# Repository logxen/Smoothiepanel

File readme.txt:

SmoothiePanel is an Open Source Hardware control interface for industrial robotic machinery. It adds a screen and user interface to allow easy control of a Smoothieboard. The current design brings a graphic LCD with RGB Backlight and changeable interface panel down to a port, optionally SPI, UART, or USB.

It is intended to control a Smoothieboard (http://smoothieware.org/), though could easily be connected to almost any logic control system. The firmware found in the firmware directory makes Smoothiepanel behave as a simple slave device that can be used via SPI, UART, or USB. As it is completely open source, however, it is very easy to write custom firmware that takes more advantage of its powerful 50MHz processor and 16 bits worth of extra gpio.

The latest version, Prototype 3, is based around the NXP LPC11UxxFBD64, which sports a 50MHz ARM Cortex-M0 processor with built in USB and up to 128KB of flash.

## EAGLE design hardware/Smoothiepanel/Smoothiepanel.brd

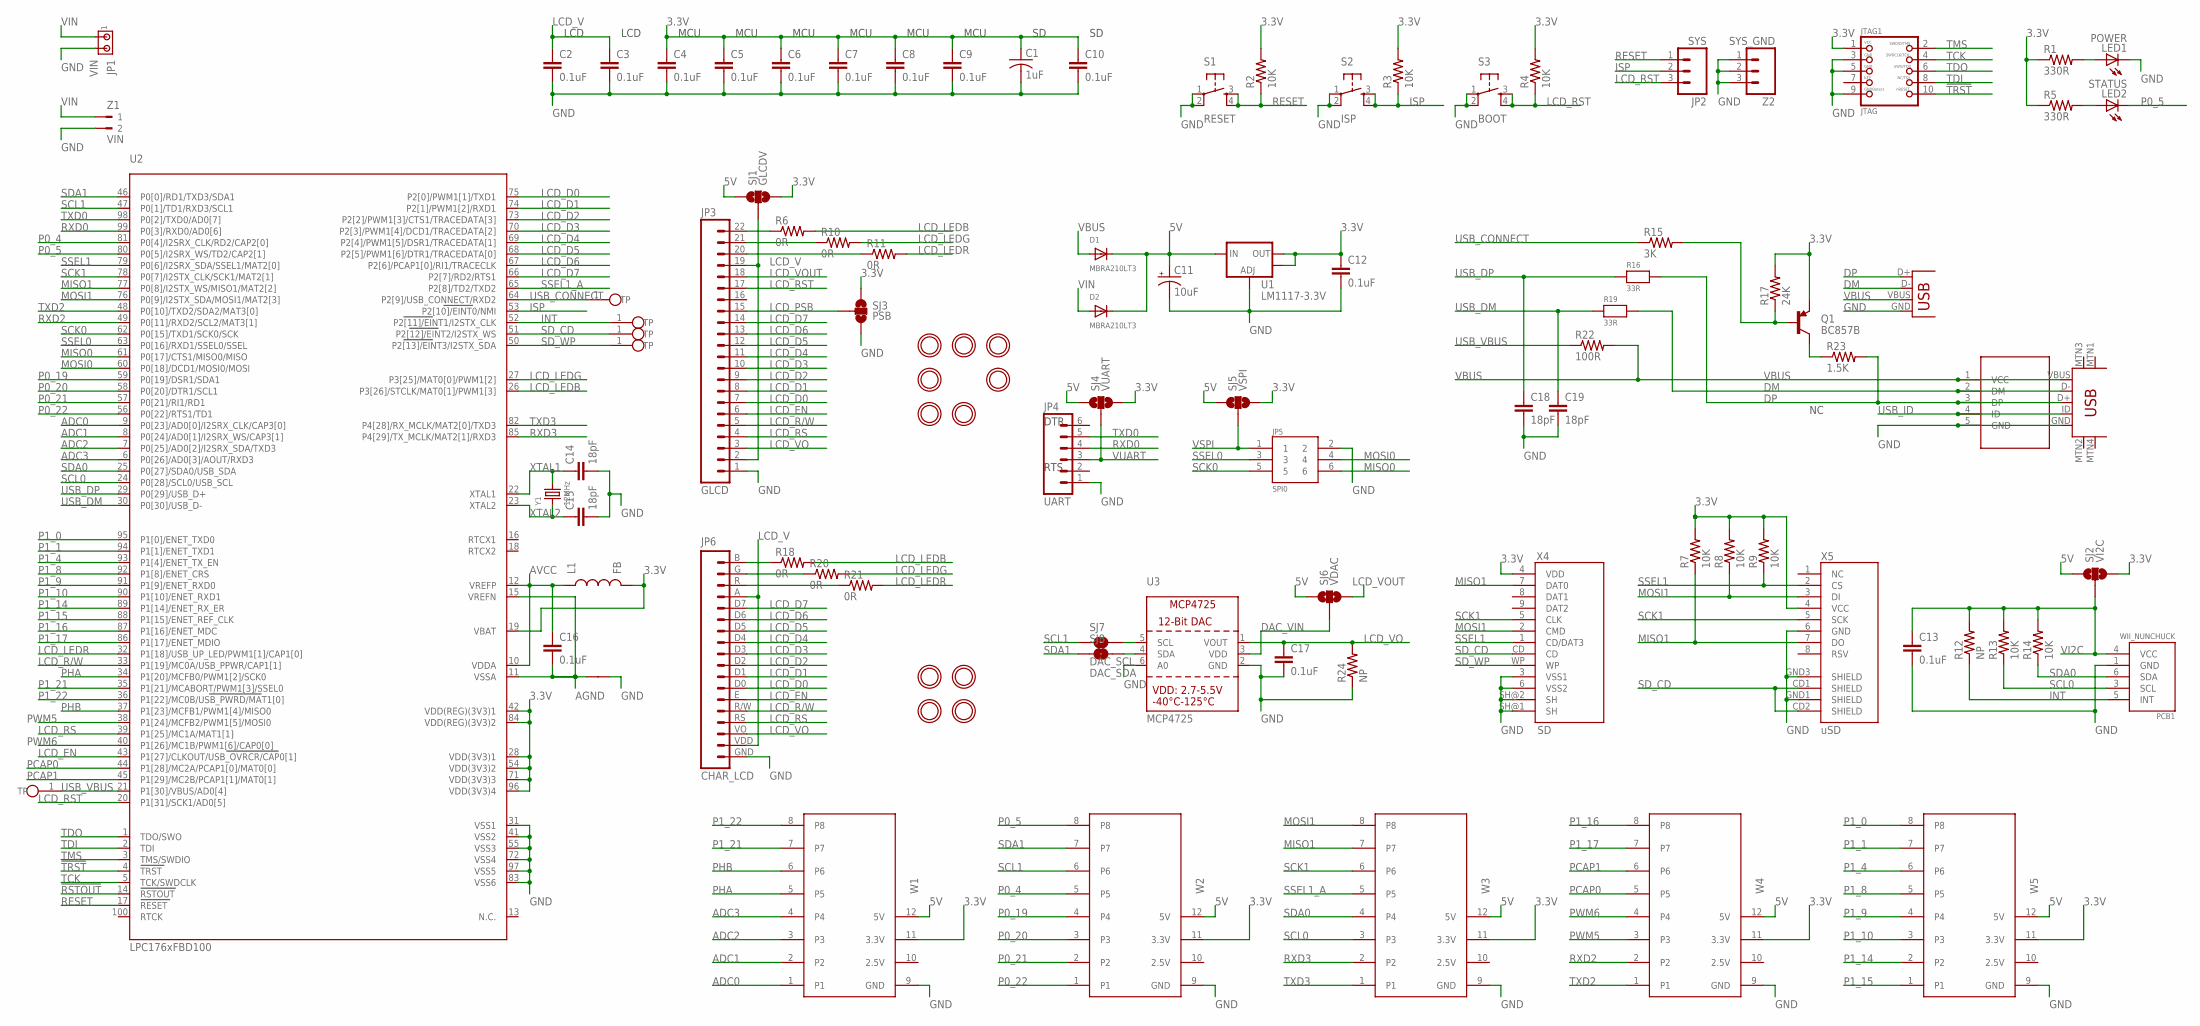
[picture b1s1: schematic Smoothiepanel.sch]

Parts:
C1: 1uF; C0805
C2, C3, C4, C5, C6, C7, C8, C9, C10, C12, C13, C16, C17: 0.1uF; 0603-CAP
C11: 10uF; EIA3216
C14, C15, C18, C19: 18pF; 0603-CAP
D1, D2: MBRA210LT3; SMADIODE
JP1: VIN; 10X02MTA
JP2: SYS; 1X03
JP3: GLCD; 1X22
JP4: UART; 1X06
JP5: SPI0; 2X3-SHROUDED
JP6: CHAR_LCD; TEXT_LCD
JTAG1: JTAG; 2X05_1.27MM_SMT
L1: FB; 0603
LED1: POWER; LED-0603
LED2: STATUS; LED-0603
MH1, MH2, MH3, MH4, MH5, MH6, MH7: MOUNTINGHOLE2.5_THICK; MOUNTINGHOLE_2.5_PLATED_THICK
MH8, MH9, MH10, MH11: MOUNTINGHOLE3.0THIN; MOUNTINGHOLE_3.0_PLATEDTHIN
N1: NET_LINK
PCB1: WII_NUNCHUCK
Q1: BC857B; SOT23-3
R1, R5: 330R; 0603-RES
R2, R3, R4, R7, R8, R9, R13, R14: 10K; 0603-RES
R6, R10, R11, R18, R20, R21: 0R; 0603-RES
R12, R24: NP; 0603-RES
R15: 3K; 0603-RES
R16, R19: 33R; _0603MP
R17: 24K; 0603-RES
R22: 100R; 0603-RES
R23: 1.5K; 0603-RES
S1: RESET; TACTILE_SWITCH_SMD
S2: ISP; TACTILE_SWITCH_SMD
S3: BOOT; TACTILE_SWITCH_SMD
SJ1: GLCDV; SJ_3
SJ2: VI2C; SJ_3
SJ3: PSB; SJ_3
SJ4: VUART; SJ_3
SJ5: VSPI; SJ_3
SJ6: VDAC; SJ_3
SJ7: DAC_SCL; SJ_2S-TRACE
SJ8: DAC_SDA; SJ_2S-TRACE
TP1, TP3, TP4, TP5, TP6: TPAD1.5; TPAD-1.5
U1: LM1117-3.3V; SOT223
U2: LPC176xFBD100; LQFP100
U3: MCP4725; SOT23-6
W1: WING1; PAPILIO-WING-8BITS-F
W2: WING2; PAPILIO-WING-8BITS-F
W3: WING3; PAPILIO-WING-8BITS-F
W4: WING4; PAPILIO-WING-8BITS-F
W5: WING5; PAPILIO-WING-8BITS-F
X1: USB-B; USB-B-PTH
X2: mUSB; USB-MINIB
X3: USB-MICROB-SMDRECEPT; USB-MICROB-RECEPT
X4: SD; SDCARD_4UCONN
X5: uSD; MICRO-SD-SOCKET-PP
Y1: 12MHz; CRYSTAL_3.2X2.5
Z1: VIN; 180-2
Z2: SYS_GND; 1X03

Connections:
3.3V: C1.1, C4.1, C5.1, C6.1, C7.1, C8.1, C9.1, C10.1, C12.1, JTAG1.1, L1.2, Q1.2 (E), R1.1, R2.2, R3.2, R4.2, R5.1, R7.2, R8.2, R9.2, R17.2, SJ1.3, SJ2.3, SJ3.1, SJ4.3, SJ5.3, U1.2 (OUT), U1.4 (OUT), U2.19 (VBAT), U2.28 (VDD(3V3)1), U2.42 (VDD(REG)(3V3)1), U2.54 (VDD(3V3)2), U2.71 (VDD(3V3)3), U2.84 (VDD(REG)(3V3)2), U2.96 (VDD(3V3)4), W1.11 (3.3V), W2.11 (3.3V), W3.11 (3.3V), W4.11 (3.3V), W5.11 (3.3V), X4.4 (VDD), X5.4 (VCC)
5V: C11.A (+), D1.C, D2.C, SJ1.1, SJ2.1, SJ4.1, SJ5.1, SJ6.1, U1.3 (IN), W1.12 (5V), W2.12 (5V), W3.12 (5V), W4.12 (5V), W5.12 (5V)
!RSTOUT!: U2.14 (RSTOUT)
!TRST!: JTAG1.10, U2.4 (TRST)
ADC0: U2.9 (P0[23]/AD0[0]/I2SRX_CLK/CAP3[0]), W1.1
ADC1: U2.8 (P0[24]/AD0[1]/I2SRX_WS/CAP3[1]), W1.2
ADC2: U2.7 (P0[25]/AD0[2]/I2SRX_SDA/TXD3), W1.3
ADC3: U2.6 (P0[26]/AD0[3]/AOUT/RXD3), W1.4
AGND: C16.2, N1.P$1, U2.11 (VSSA), U2.15 (VREFN)
AVCC: C16.1, L1.1, U2.10 (VDDA), U2.12 (VREFP)
DAC_SCL_RES: SJ7.2, U3.5 (SCL)
DAC_SDA_RES: SJ8.2, U3.4 (SDA)
DAC_VIN: SJ6.2, U3.3 (VDD)
DM: R19.2, X1.D-, X2.D-, X3.2 (DM)
DP: R16.2, R23.2, X1.D+, X2.D+, X3.3 (DP)
GND: C1.2, C2.2, C3.2, C4.2, C5.2, C6.2, C7.2, C8.2, C9.2, C10.2, C11.C (-), C12.2, C13.2, C14.2, C15.2, C17.2, C18.2, C19.2, JP1.2, JP3.1, JP4.1, JP5.2, JP6.GND (1), JTAG1.3, JTAG1.5, JTAG1.9, LED1.C, N1.P$2, PCB1.1 (GND), R24.1, S1.1, S1.2, S2.1, S2.2, S3.1, S3.2, SJ3.3, U1.1 (ADJ), U2.31 (VSS1), U2.41 (VSS2), U2.55 (VSS3), U2.72 (VSS4), U2.83 (VSS6), U2.97 (VSS5), U3.2 (GND), U3.6 (A0), W1.9 (GND), W2.9 (GND), W3.9 (GND), W4.9 (GND), W5.9 (GND), X1.GND, X2.GND, X3.5 (GND), X4.3 (VSS1), X4.6 (VSS2), X4.SH@1 (SH), X4.SH@2 (SH), X5.6 (GND), X5.GND1 (SHIELD), X5.GND3 (SHIELD), Z1.2, Z2.1, Z2.2, Z2.3
INT: PCB1.5 (INT), R12.1, TP4.1, U2.52 (P2[11]/EINT1/I2STX_CLK)
ISP: JP2.2, R3.1, S2.3, S2.4, U2.53 (P2[10]/EINT0/NMI)
LCD_D0: JP3.7, JP6.D0 (7), U2.75 (P2[0]/PWM1[1]/TXD1)
LCD_D1: JP3.8, JP6.D1 (8), U2.74 (P2[1]/PWM1[2]/RXD1)
LCD_D2: JP3.9, JP6.D2 (9), U2.73 (P2[2]/PWM1[3]/CTS1/TRACEDATA[3])
LCD_D3: JP3.10, JP6.D3 (10), U2.70 (P2[3]/PWM1[4]/DCD1/TRACEDATA[2])
LCD_D4: JP3.11, JP6.D4 (11), U2.69 (P2[4]/PWM1[5]/DSR1/TRACEDATA[1])
LCD_D5: JP3.12, JP6.D5 (12), U2.68 (P2[5]/PWM1[6]/DTR1/TRACEDATA[0])
LCD_D6: JP3.13, JP6.D6 (13), U2.67 (P2[6]/PCAP1[0]/RI1/TRACECLK)
LCD_D7: JP3.14, JP6.D7 (14), U2.66 (P2[7]/RD2/RTS1)
LCD_EN: JP3.6, JP6.E (6), U2.43 (P1[27]/CLKOUT/USB_OVRCR/CAP0[1])
LCD_LEDB: R6.2, R18.2, U2.26 (P3[26]/STCLK/MAT0[1]/PWM1[3])
LCD_LEDB_RES: JP3.22, R6.1
LCD_LEDB_RES1: JP6.B (18), R18.1
LCD_LEDG: R10.2, R20.2, U2.27 (P3[25]/MAT0[0]/PWM1[2])
LCD_LEDG_RES: JP3.21, R10.1
LCD_LEDG_RES1: JP6.G (17), R20.1
LCD_LEDR: R11.2, R21.2, U2.32 (P1[18]/USB_UP_LED/PWM1[1]/CAP1[0])
LCD_LEDR_RES: JP3.20, R11.1
LCD_LEDR_RES1: JP6.R (16), R21.1
LCD_PSB: JP3.15, SJ3.2
LCD_R/W: JP3.5, JP6.R/W (5), U2.33 (P1[19]/MC0A/USB_PPWR/CAP1[1])
LCD_RS: JP3.4, JP6.RS (4), U2.39 (P1[25]/MC1A/MAT1[1])
LCD_RST: JP2.3, JP3.17, R4.1, S3.3, S3.4, U2.20 (P1[31]/SCK1/AD0[5])
LCD_V: C2.1, C3.1, JP3.2, JP3.19, JP6.A (15), JP6.VDD (2), SJ1.2
LCD_VO: C17.1, JP3.3, JP6.VO (3), R24.2, U3.1 (VOUT)
LCD_VOUT: JP3.18, SJ6.3
LED1_R: LED1.A, R1.2
LED2_R: LED2.A, R5.2
MISO0: JP5.6, U2.61 (P0[17]/CTS1/MISO0/MISO)
MISO1: R7.1, U2.77 (P0[8]/I2STX_WS/MISO1/MAT2[2]), W3.7, X4.7 (DAT0), X5.7 (DO)
MOSI0: JP5.4, U2.60 (P0[18]/DCD1/MOSI0/MOSI)
MOSI1: R8.1, U2.76 (P0[9]/I2STX_SDA/MOSI1/MAT2[3]), W3.8, X4.2 (CMD), X5.3 (DI)
P0_4: U2.81 (P0[4]/I2SRX_CLK/RD2/CAP2[0]), W2.5
P0_5: LED2.C, U2.80 (P0[5]/I2SRX_WS/TD2/CAP2[1]), W2.8
P0_19: U2.59 (P0[19]/DSR1/SDA1), W2.4
P0_20: U2.58 (P0[20]/DTR1/SCL1), W2.3
P0_21: U2.57 (P0[21]/RI1/RD1), W2.2
P0_22: U2.56 (P0[22]/RTS1/TD1), W2.1
P1_0: U2.95 (P1[0]/ENET_TXD0), W5.8
P1_1: U2.94 (P1[1]/ENET_TXD1), W5.7
P1_4: U2.93 (P1[4]/ENET_TX_EN), W5.6
P1_8: U2.92 (P1[8]/ENET_CRS), W5.5
P1_9: U2.91 (P1[9]/ENET_RXD0), W5.4
P1_10: U2.90 (P1[10]/ENET_RXD1), W5.3
P1_14: U2.89 (P1[14]/ENET_RX_ER), W5.2
P1_15: U2.88 (P1[15]/ENET_REF_CLK), W5.1
P1_16: U2.87 (P1[16]/ENET_MDC), W4.8
P1_17: U2.86 (P1[17]/ENET_MDIO), W4.7
P1_21: U2.35 (P1[21]/MCABORT/PWM1[3]/SSEL0), W1.7
P1_22: U2.36 (P1[22]/MC0B/USB_PWRD/MAT1[0]), W1.8
PCAP0: U2.44 (P1[28]/MC2A/PCAP1[0]/MAT0[0]), W4.5
PCAP1: U2.45 (P1[29]/MC2B/PCAP1[1]/MAT0[1]), W4.6
PHA: U2.34 (P1[20]/MCFB0/PWM1[2]/SCK0), W1.5
PHB: U2.37 (P1[23]/MCFB1/PWM1[4]/MISO0), W1.6
PWM5: U2.38 (P1[24]/MCFB2/PWM1[5]/MOSI0), W4.3
PWM6: U2.40 (P1[26]/MC1B/PWM1[6]/CAP0[0]), W4.4
RESET: JP2.1, R2.1, S1.3, S1.4, U2.17 (RESET)
RXD0: JP4.4, U2.99 (P0[3]/RXD0/AD0[6])
RXD2: U2.49 (P0[11]/RXD2/SCL2/MAT3[1]), W4.2
RXD3: U2.85 (P4[29]/TX_MCLK/MAT2[1]/RXD3), W3.2
SCK0: JP5.5, U2.62 (P0[15]/TXD1/SCK0/SCK)
SCK1: U2.78 (P0[7]/I2STX_CLK/SCK1/MAT2[1]), W3.6, X4.5 (CLK), X5.5 (SCK)
SCL0: PCB1.3 (SCL), R13.1, U2.24 (P0[28]/SCL0/USB_SCL), W3.3
SCL1: SJ7.1, U2.47 (P0[1]/TD1/RXD3/SCL1), W2.6
SDA0: PCB1.6 (SDA), R14.1, U2.25 (P0[27]/SDA0/USB_SDA), W3.4
SDA1: SJ8.1, U2.46 (P0[0]/RD1/TXD3/SDA1), W2.7
SD_CD: TP5.1, U2.51 (P2[12]/EINT2/I2STX_WS), X4.CD, X5.CD1 (SHIELD), X5.CD2 (SHIELD)
SD_WP: TP6.1, U2.50 (P2[13]/EINT3/I2STX_SDA), X4.WP
SSEL0: JP5.3, U2.63 (P0[16]/RXD1/SSEL0/SSEL)
SSEL1: R9.1, U2.79 (P0[6]/I2SRX_SDA/SSEL1/MAT2[0]), X4.1 (CD/DAT3), X5.2 (CS)
SSEL1_A: U2.65 (P2[8]/TD2/TXD2), W3.5
TCK: JTAG1.4, U2.5 (TCK/SWDCLK)
TDI: JTAG1.8, U2.2 (TDI)
TDO: JTAG1.6, U2.1 (TDO/SWO)
TMS: JTAG1.2, U2.3 (TMS/SWDIO)
TXD0: JP4.5, U2.98 (P0[2]/TXD0/AD0[7])
TXD2: U2.48 (P0[10]/TXD2/SDA2/MAT3[0]), W4.1
TXD3: U2.82 (P4[28]/RX_MCLK/MAT2[0]/TXD3), W3.1
USB_CONNECT: R15.1, TP3.1, U2.64 (P2[9]/USB_CONNECT/RXD2)
USB_CONNECT_BASE: Q1.1 (B), R15.2, R17.1
USB_CONNECT_COLLECTOR: Q1.3 (C), R23.1
USB_DM: C19.1, R19.1, U2.30 (P0[30]/USB_D-)
USB_DP: C18.1, R16.1, U2.29 (P0[29]/USB_D+)
USB_ID: X2.ID, X3.4 (ID)
USB_VBUS: R22.1, TP1.1, U2.21 (P1[30]/VBUS/AD0[4])
VBUS: D1.A, R22.2, X1.VBUS, X2.VBUS, X3.1 (VCC)
VI2C: C13.1, PCB1.4 (VCC), R12.2, R13.2, R14.2, SJ2.2
VIN: D2.A, JP1.1, Z1.1
VSPI: JP5.1, SJ5.2
VUART: JP4.3, SJ4.2
XTAL1: C14.1, U2.22 (XTAL1), Y1.2
XTAL2: C15.1, U2.23 (XTAL2), Y1.1

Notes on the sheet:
DTR
RTS
LCD
MCU

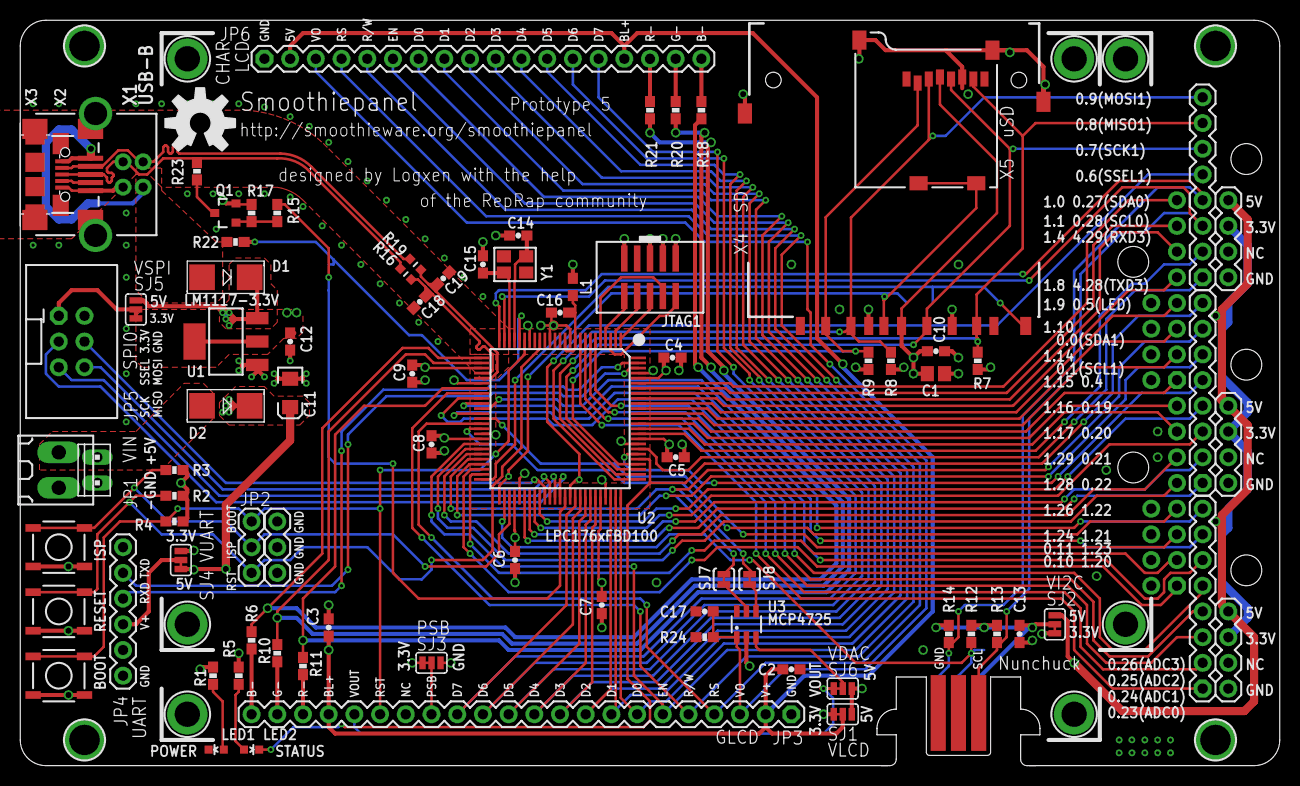
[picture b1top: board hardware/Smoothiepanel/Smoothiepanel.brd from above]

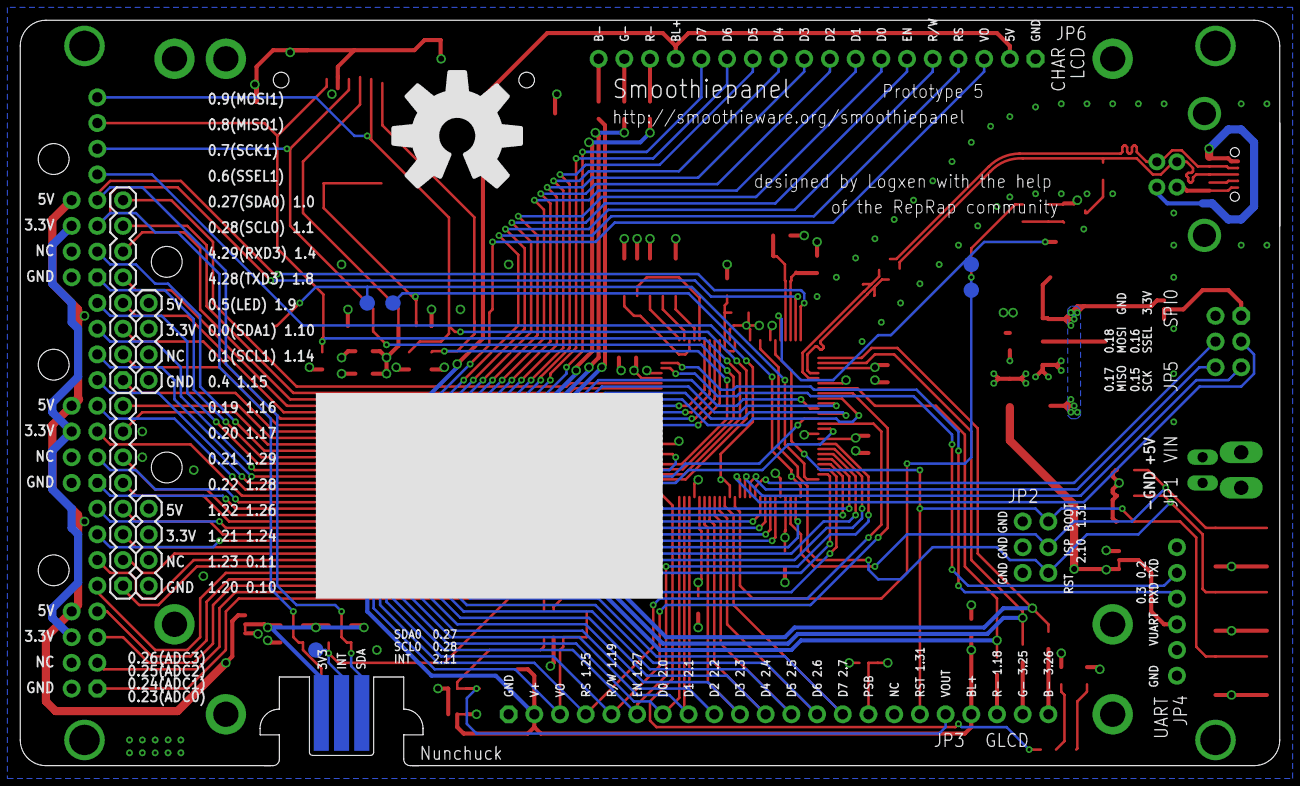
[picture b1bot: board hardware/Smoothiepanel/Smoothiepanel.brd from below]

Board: 4 copper layers, 124.5 x 73.7 mm, 103 parts (8 on the bottom side), 108 nets.

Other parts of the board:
U$1: OSHW-LOGO-HUGE
U$2: OSHW-LOGO-L

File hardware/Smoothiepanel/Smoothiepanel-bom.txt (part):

Partlist exported from C:/Users/Logxen/Documents/eagle/Smoothie/Smoothiepanel/Smoothiepanel/Smoothiepanel-Proto5.sch at 7/15/2014 9:03:24 AM

Qty Value         Device              Package            Parts                                                   Description                                                                                                                                                                                               MF MPN OC_FARNELL OC_NEWARK PROD_ID    VALUE
13  0.1uF         CAP0603-CAP         0603-CAP           C2, C3, C4, C5, C6, C7, C8, C9, C10, C12, C13, C16, C17 Capacitor                                                                                                                                                                                                                                             
6   0R            RESISTOR0603-RES    0603-RES           R6, R10, R11, R18, R20, R21                             Resistor                                                                                                                                                                                                                                              
1   1.5K          RESISTOR0603-RES    0603-RES           R23                                                     Resistor                                                                                                                                                                                                                                              
1   100R          RESISTOR0603-RES    0603-RES           R22                                                     Resistor                                                                                                                                                                                                                                              
8   10K           RESISTOR0603-RES    0603-RES           R2, R3, R4, R7, R8, R9, R13, R14                        Resistor                                                                                                                                                                                                                                              
1   10uF          CAP_POL1206         EIA3216            C11                                                     Capacitor Polarized                                                                                                                                                                                                                                   
1   12MHz         CRYSTALTHIN         CRYSTAL_3.2X2.5    Y1                                                      Crystals                                                                                                                                                                                                                                              
4   18pF          CAP0603-CAP         0603-CAP           C14, C15, C18, C19                                      Capacitor                                                                                                                                                                                                                                             
1   1uF           C-USC0805           C0805              C1                                                      CAPACITOR, American symbol                                                                                                                                                                                                                            
1   24K           RESISTOR0603-RES    0603-RES           R17                                                     Resistor                                                                                                                                                                                                                                              
2   330R          RESISTOR0603-RES    0603-RES           R1, R5                                                  Resistor                                                                                                                                                                                                                                              
2   33R           RESISTOR_0603MP     _0603MP            R16, R19                                                Resistors                                                                                                                                                                                                                                             
1   3K            RESISTOR0603-RES    0603-RES           R15                                                     Resistor                                                                                                                                                                                                                                              
1   BC857B        TRANSISTOR_PNPSMD   SOT23-3            Q1                                                      Generic PNP BJT. Double check pinouts against datasheets- not all devices are the same!                                                                                                                                                               
1   FB            INDUCTOR0603        0603               L1                                                      Inductors                                                                                                                                                                                                                                             
1   LM1117-3.3V   V_REG_LM1117SOT223  SOT223             U1                                                      Voltage Regulator LM1117                                                                                                                                                                                                                              
1   LPC176xFBD100 LPC1768             LQFP100            U2                                                      LPC1768 100 MHz 32-bit ARM Cortex-M3 based microcontroller featuring a high level of integration and low power consumption. 512 kB Flash, 64 kB SRAM, USB Device/Host/OTG, Ethernet, CAN, I2S, 10-bit DAC                                             
2   MBRA210LT3    DIODESMA            SMADIODE           D1, D2                                                  Diode                                                                                                                                                                                                                                                 
1   MCP4725       DAC_MCP4725         SOT23-6            U3                                                      MCP4725 - 12-Bit I2C DAC with on-board EEPROM                                                                                                                                                                                                         
1   POWER         LED0603             LED-0603           LED1                                                    LEDs                                                                                                                                                                                                                                                  
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
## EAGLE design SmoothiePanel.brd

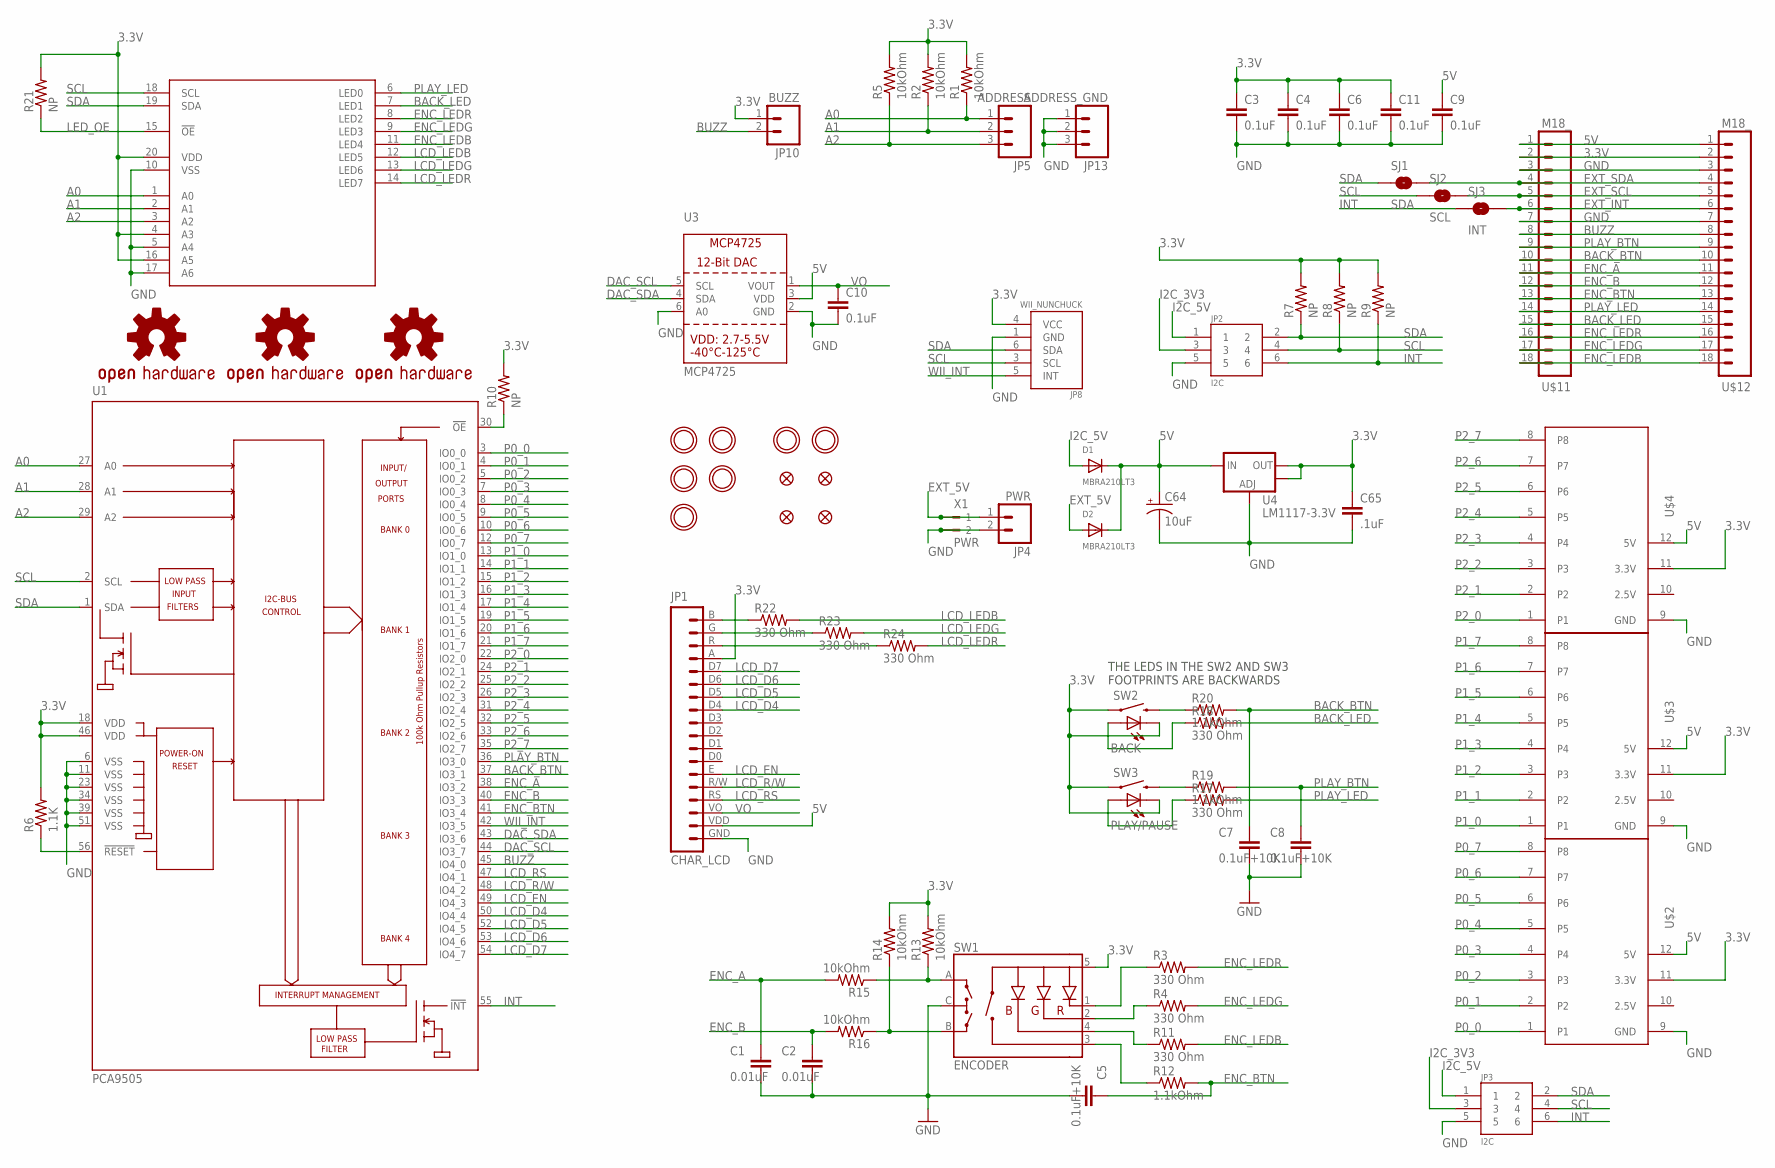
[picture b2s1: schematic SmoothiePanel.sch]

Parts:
C1, C2: 0.01uF; C0603
C3, C4, C6, C9, C10, C11: 0.1uF; 0603-CAP
C5, C7, C8: 0.1uF+10K; C0603
C64: 10uF; EIA3216
C65: .1uF; C0603
D1, D2: MBRA210LT3; SMADIODE
JP1: CHAR_LCD; TEXT_LCD
JP2, JP3: I2C; 2X3-SHROUDED
JP4: PWR; 1X02_LONGPADS
JP5: ADDRESS; 1X03
JP8: WII_NUNCHUCK
JP9, JP11, JP12, JP14: FIDUCIAL1X2; FIDUCIAL-1X2
JP10: BUZZ; 1X02_XTRA_BIG
JP13: ADDRESS_GND; 1X03
R1, R2, R5, R13, R14, R15, R16: 10kOhm; R0603
R3, R4, R11, R17, R18, R22, R23, R24: 330 Ohm; R0603
R6: 1.1K; R0603
R7, R8, R9, R10, R21: NP; R0603
R12, R19, R20: 1.1kOhm; R0603
SJ1: SDA; SJ_2S-NO
SJ2: SCL; SJ_2S-NO
SJ3: INT; SJ_2S-NO
SW1: ENCODER; ENCODER_LED_3
SW2: BACK; TACTILE-PTH-LED-12MM
SW3: PLAY/PAUSE; TACTILE-PTH-LED-12MM
U1: PCA9505; TSSOP56-6
U2: PCA9634-TSSOP20; TSSOP20
U3: MCP4725; SOT23-6
U4: LM1117-3.3V; SOT223
U$1, U$8, U$10: OSHW-LOGOL; OSHW-LOGO-L
U$2, U$3, U$4: PAPILIO-WING-8BITS
U$5, U$9, U$13, U$14, U$15: MOUNTINGHOLE3.0THIN; MOUNTINGHOLE_3.0_PLATEDTHIN
U$6, U$7: MOUNTINGHOLE2.5_THICK; MOUNTINGHOLE_2.5_PLATED_THICK
U$11, U$12: M18_; 1X18
X1: PWR; 180-2

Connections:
3.3V: C3.1, C4.1, C6.1, C11.1, C65.1, JP1.A (15), JP8.4 (VCC), JP10.1, R1.2, R2.2, R5.2, R6.2, R7.2, R8.2, R9.2, R10.2, R13.2, R14.2, R21.2, SW1.5 (+), SW2.4 (1), SW2.C, SW3.4 (1), SW3.C, U1.18 (VDD), U1.46 (VDD), U2.4 (A3), U2.16 (A5), U2.20 (VDD), U4.2 (OUT), U4.4 (OUT), U$2.11 (3.3V), U$3.11 (3.3V), U$4.11 (3.3V), U$11.2, U$12.2
5V: C9.1, C64.A (+), D1.C, D2.C, JP1.VDD (2), U3.3 (VDD), U4.3 (IN), U$2.12 (5V), U$3.12 (5V), U$4.12 (5V), U$11.1, U$12.1
A0: JP5.1, R1.1, U1.27 (A0), U2.1 (A0)
A1: JP5.2, R2.1, U1.28 (A1), U2.2 (A1)
A2: JP5.3, R5.1, U1.29 (A2), U2.3 (A2)
BACK_BTN: C7.1, R20.2, U1.37 (IO3_1), U$11.10, U$12.10
BACK_BTN_RES: R20.1, SW2.2
BACK_LED: R18.2, U2.7 (LED1), U$11.15, U$12.15
BACK_LED_RES: R18.1, SW2.A
BUZZ: JP10.2, U1.45 (IO4_0), U$11.8, U$12.8
DAC_SCL: U1.44 (IO3_7), U3.5 (SCL)
DAC_SDA: U1.43 (IO3_6), U3.4 (SDA)
ENC_A: C1.1, R15.2, U1.38 (IO3_2), U$11.11, U$12.11
ENC_A_RES: R13.1, R15.1, SW1.A
ENC_B: C2.1, R16.2, U1.40 (IO3_3), U$11.12, U$12.12
ENC_BTN: C5.1, R12.2, U1.41 (IO3_4), U$11.13, U$12.13
ENC_BTN_RES: R12.1, SW1.3 (SW)
ENC_B_RES: R14.1, R16.1, SW1.B
ENC_LEDB: R11.2, U2.11 (LED4), U$11.18, U$12.18
ENC_LEDB_RES: R11.1, SW1.4 (-B)
ENC_LEDG: R4.2, U2.9 (LED3), U$11.17, U$12.17
ENC_LEDG_RES: R4.1, SW1.2 (-G)
ENC_LEDR: R3.2, U2.8 (LED2), U$11.16, U$12.16
ENC_LEDR_RES: R3.1, SW1.1 (-R)
EXT_5V: D2.A, JP4.1, X1.1
EXT_INT: SJ3.2, U$11.6, U$12.6
EXT_SCL: SJ2.2, U$11.5, U$12.5
EXT_SDA: SJ1.2, U$11.4, U$12.4
GND: C1.2, C2.2, C3.2, C4.2, C5.2, C6.2, C7.2, C8.2, C9.2, C10.2, C11.2, C64.C (-), C65.2, JP1.GND (1), JP2.5, JP3.5, JP4.2, JP8.1 (GND), JP13.1, JP13.2, JP13.3, SW1.C, U1.6 (VSS), U1.11 (VSS), U1.23 (VSS), U1.34 (VSS), U1.39 (VSS), U1.51 (VSS), U2.5 (A4), U2.10 (VSS), U2.17 (A6), U3.2 (GND), U3.6 (A0), U4.1 (ADJ), U$2.9 (GND), U$3.9 (GND), U$4.9 (GND), U$11.3, U$11.7, U$12.3, U$12.7, X1.2
I2C_3V3: JP2.3, JP3.3
I2C_5V: D1.A, JP2.1, JP3.1
INT: JP2.6, JP3.6, R9.1, SJ3.1, U1.55 (!INT)
LCD_D4: JP1.D4 (11), U1.50 (IO4_4)
LCD_D5: JP1.D5 (12), U1.52 (IO4_5)
LCD_D6: JP1.D6 (13), U1.53 (IO4_6)
LCD_D7: JP1.D7 (14), U1.54 (IO4_7)
LCD_EN: JP1.E (6), U1.49 (IO4_3)
LCD_LEDB: R22.2, U2.12 (LED5)
LCD_LEDB_RES: JP1.B (18), R22.1
LCD_LEDG: R23.2, U2.13 (LED6)
LCD_LEDG_RES: JP1.G (17), R23.1
LCD_LEDR: R24.2, U2.14 (LED7)
LCD_LEDR_RES: JP1.R (16), R24.1
LCD_R/W: JP1.R/W (5), U1.48 (IO4_2)
LCD_RS: JP1.RS (4), U1.47 (IO4_1)
LED_OE: R21.1, U2.15 (!OE!)
OE: R10.1, U1.30 (!OE)
P0_0: U1.3 (IO0_0), U$2.1
P0_1: U1.4 (IO0_1), U$2.2
P0_2: U1.5 (IO0_2), U$2.3
P0_3: U1.7 (IO0_3), U$2.4
P0_4: U1.8 (IO0_4), U$2.5
P0_5: U1.9 (IO0_5), U$2.6
P0_6: U1.10 (IO0_6), U$2.7
P0_7: U1.12 (IO0_7), U$2.8
P1_0: U1.13 (IO1_0), U$3.1
P1_1: U1.14 (IO1_1), U$3.2
P1_2: U1.15 (IO1_2), U$3.3
P1_3: U1.16 (IO1_3), U$3.4
P1_4: U1.17 (IO1_4), U$3.5
P1_5: U1.19 (IO1_5), U$3.6
P1_6: U1.20 (IO1_6), U$3.7
P1_7: U1.21 (IO1_7), U$3.8
P2_0: U1.22 (IO2_0), U$4.1
P2_1: U1.24 (IO2_1), U$4.2
P2_2: U1.25 (IO2_2), U$4.3
P2_3: U1.26 (IO2_3), U$4.4
P2_4: U1.31 (IO2_4), U$4.5
P2_5: U1.32 (IO2_5), U$4.6
P2_6: U1.33 (IO2_6), U$4.7
P2_7: U1.35 (IO2_7), U$4.8
PLAY_BTN: C8.1, R19.2, U1.36 (IO3_0), U$11.9, U$12.9
PLAY_BTN_RES: R19.1, SW3.2
PLAY_LED: R17.2, U2.6 (LED0), U$11.14, U$12.14
PLAY_LED_RES: R17.1, SW3.A
RESET: R6.1, U1.56 (!RESET)
SCL: JP2.4, JP3.4, JP8.3 (SCL), R8.1, SJ2.1, U1.2 (SCL), U2.18 (SCL)
SDA: JP2.2, JP3.2, JP8.6 (SDA), R7.1, SJ1.1, U1.1 (SDA), U2.19 (SDA)
VO: C10.1, JP1.VO (3), U3.1 (VOUT)
WII_INT: JP8.5 (INT), U1.42 (IO3_5)

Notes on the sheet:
THE LEDS IN THE SW2 AND SW3 FOOTPRINTS ARE BACKWARDS

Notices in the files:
parts and their libraries:
SparkFun: Licensing: CC v3.0 Share-Alike You are welcome to use this library for commercial purposes.
microbuilder: This work is placed in the public domain, and may be freely used for commercial and non-commercial work with the following conditions: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
